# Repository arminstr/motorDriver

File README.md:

# Universal Motor Driver
This repository contains all files needed to order and build a motor driver which can be used with closed-loop stepper motors.

## Hardware
The driver is designed for board mount. THT pins are used for solder connection to a carrier board. Molex picoblade connectors are used for the encoder and CAN communication lines. These will be replaced by solder pins in a future revision.

## Software
Software features will be added continuously. Currently Microstepping and current control are implemented. Next added feature will be CAN communication. 

### Current State of Development

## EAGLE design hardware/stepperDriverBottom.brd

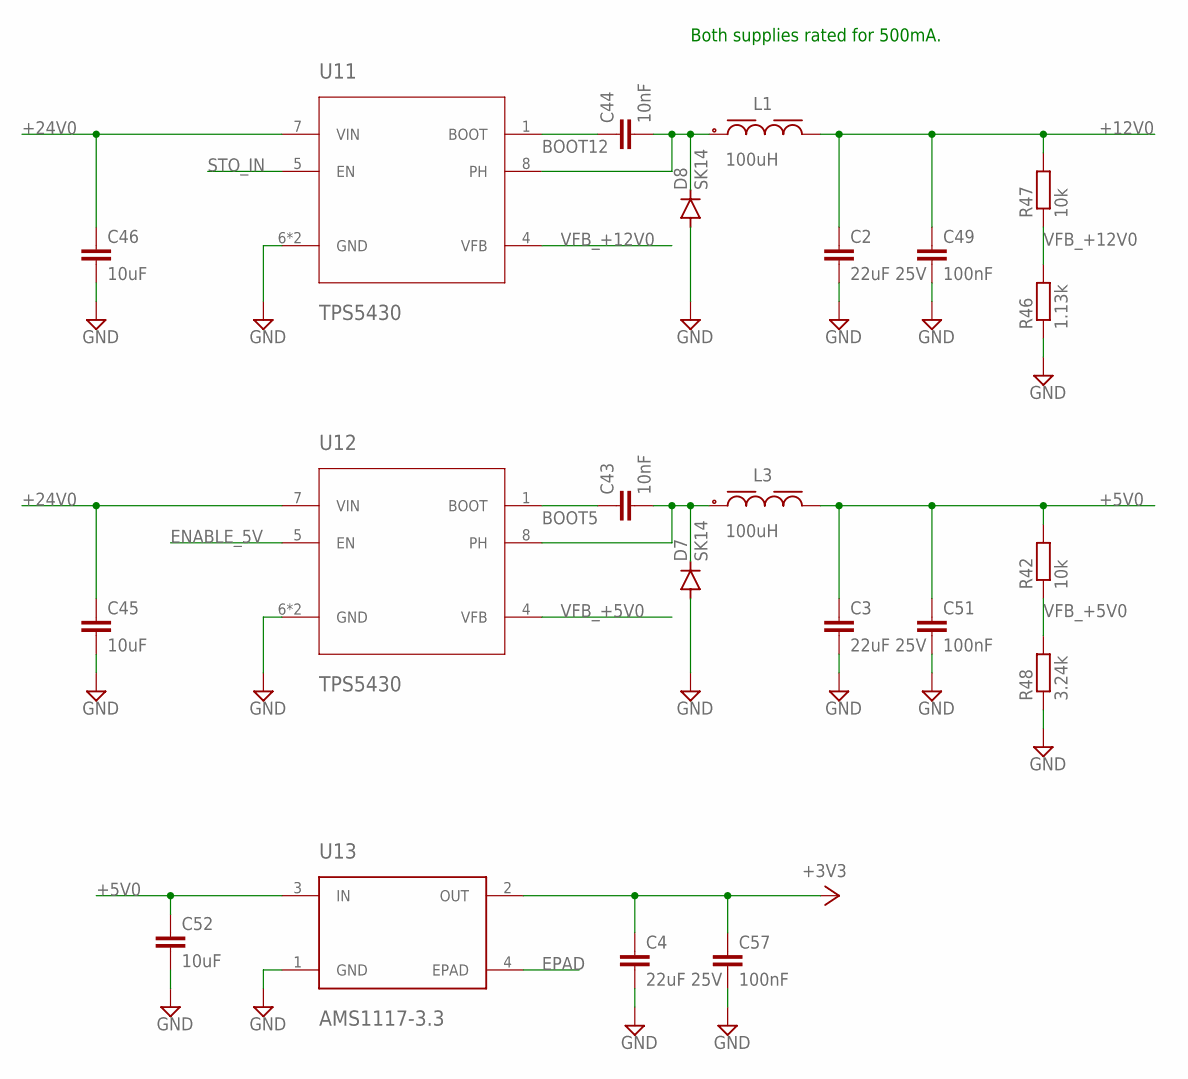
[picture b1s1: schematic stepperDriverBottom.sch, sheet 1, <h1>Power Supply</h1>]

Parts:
C2, C3, C4: 22uF 25V; C0805
C43, C44: 10nF; C0402
C45, C46, C52: 10uF; C1206
C49, C51, C57: 100nF; C0402
D7, D8: SK14; DO-214AC
L1, L3: 100uH; WE-LQS_6028
R42, R47: 10k; R0402
R46: 1.13k; R0402
R48: 3.24k; R0402
U11, U12: TPS5430; DDA8_3P1X2P4
U13: AMS1117-3.3; SOT223

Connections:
+3V3: C4.1, C57.1, U13.2 (OUT); also elsewhere on the board
+5V0: C3.1, C51.1, C52.1, L3.2, R42.2, U13.3 (IN); also elsewhere on the board
+12V0: C2.1, C49.1, L1.2, R47.2; also elsewhere on the board
+24V0: C45.1, C46.1, U11.7 (VIN), U12.7 (VIN); also elsewhere on the board
BOOT5: C43.1, U12.1 (BOOT)
BOOT12: C44.1, U11.1 (BOOT)
ENABLE_5V: U12.5 (EN)
EPAD: U13.4 (EPAD)
GND: C2.2, C3.2, C4.2, C45.2, C46.2, C49.2, C51.2, C52.2, C57.2, D7.A, D8.A, R46.1, R48.1, U11.6 (GND), U11.EPAD (GND), U12.6 (GND), U12.EPAD (GND), U13.1 (GND); also elsewhere on the board
unnamed: C44.2, D8.C, L1.1, U11.8 (PH)
unnamed: C43.2, D7.C, L3.1, U12.8 (PH)
STO_IN: U11.5 (EN); also elsewhere on the board
VFB_+5V0: R42.1, R48.2, U12.4 (VFB)
VFB_+12V0: R46.2, R47.1, U11.4 (VFB)

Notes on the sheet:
Both supplies rated for 500mA.

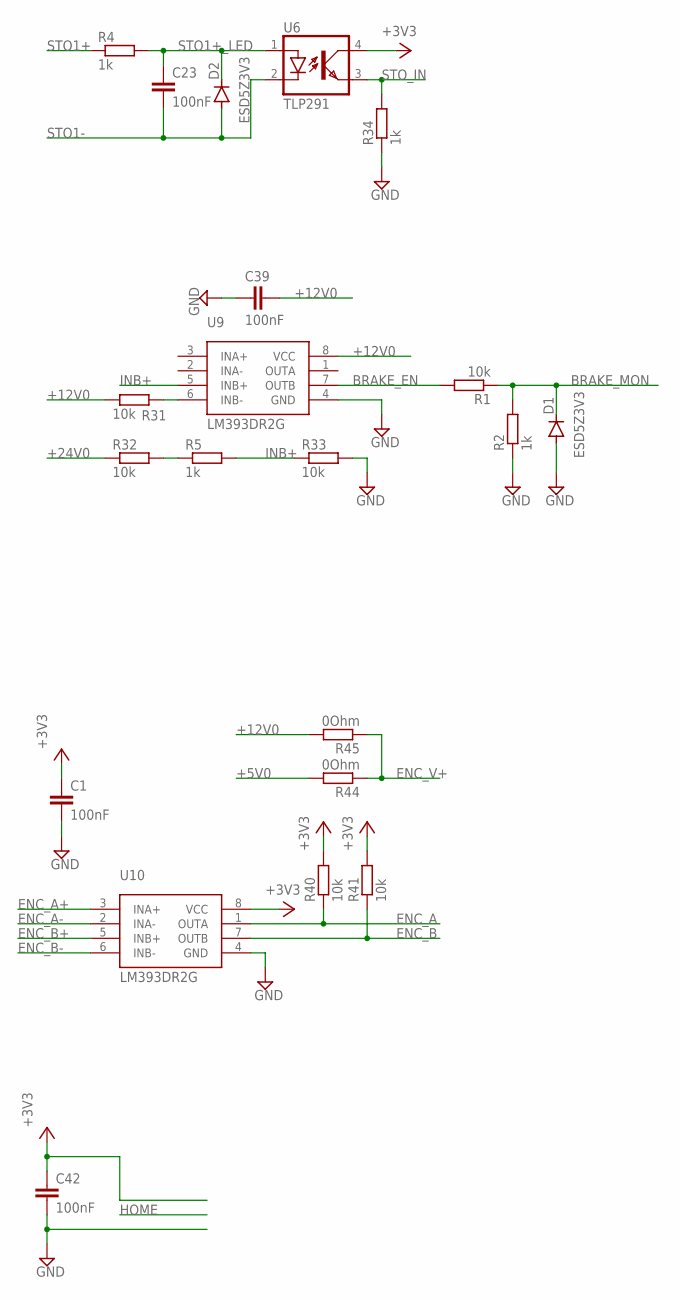
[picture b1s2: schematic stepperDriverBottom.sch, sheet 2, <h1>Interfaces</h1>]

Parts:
C1, C23, C39, C42: 100nF; C0402
D1, D2: ESD5Z3V3; SOD523
R1, R31, R32, R33, R40, R41: 10k; R0402
R2, R4, R5, R34: 1k; R0402
R44, R45: 0Ohm; R0402
U6: TLP291; SOIC127P700X210-4N
U9, U10: LM393DR2G; SOIC127P600X175-8N

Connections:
+3V3: C1.1, C42.1, R40.2, R41.2, U6.4 (COL), U10.8 (VCC); also elsewhere on the board
+5V0: R44.2; also elsewhere on the board
+12V0: C39.1, R31.1, R45.2, U9.8 (VCC); also elsewhere on the board
+24V0: R32.1; also elsewhere on the board
BRAKE_EN: R1.2, U9.7 (OUTB); also elsewhere on the board
BRAKE_MON: D1.C, R1.1, R2.2; also elsewhere on the board
ENC_A: R40.1, U10.1 (OUTA); also elsewhere on the board
ENC_A+: U10.3 (INA+); also elsewhere on the board
ENC_A-: U10.2 (INA-); also elsewhere on the board
ENC_B: R41.1, U10.7 (OUTB); also elsewhere on the board
ENC_B+: U10.5 (INB+); also elsewhere on the board
ENC_B-: U10.6 (INB-); also elsewhere on the board
ENC_V+: R44.1, R45.1; also elsewhere on the board
GND: C1.2, C39.2, C42.2, D1.A, R2.1, R33.2, R34.1, U9.4 (GND), U10.4 (GND); also elsewhere on the board
INB+: R5.2, R33.1, U9.5 (INB+)
unnamed: R5.1, R32.2
unnamed: R31.2, U9.6 (INB-)
STO1+: R4.1; also elsewhere on the board
STO1+_LED: C23.1, D2.C, R4.2, U6.1 (A)
STO1-: C23.2, D2.A, U6.2 (C); also elsewhere on the board
STO_IN: R34.2, U6.3 (EMIT); also elsewhere on the board

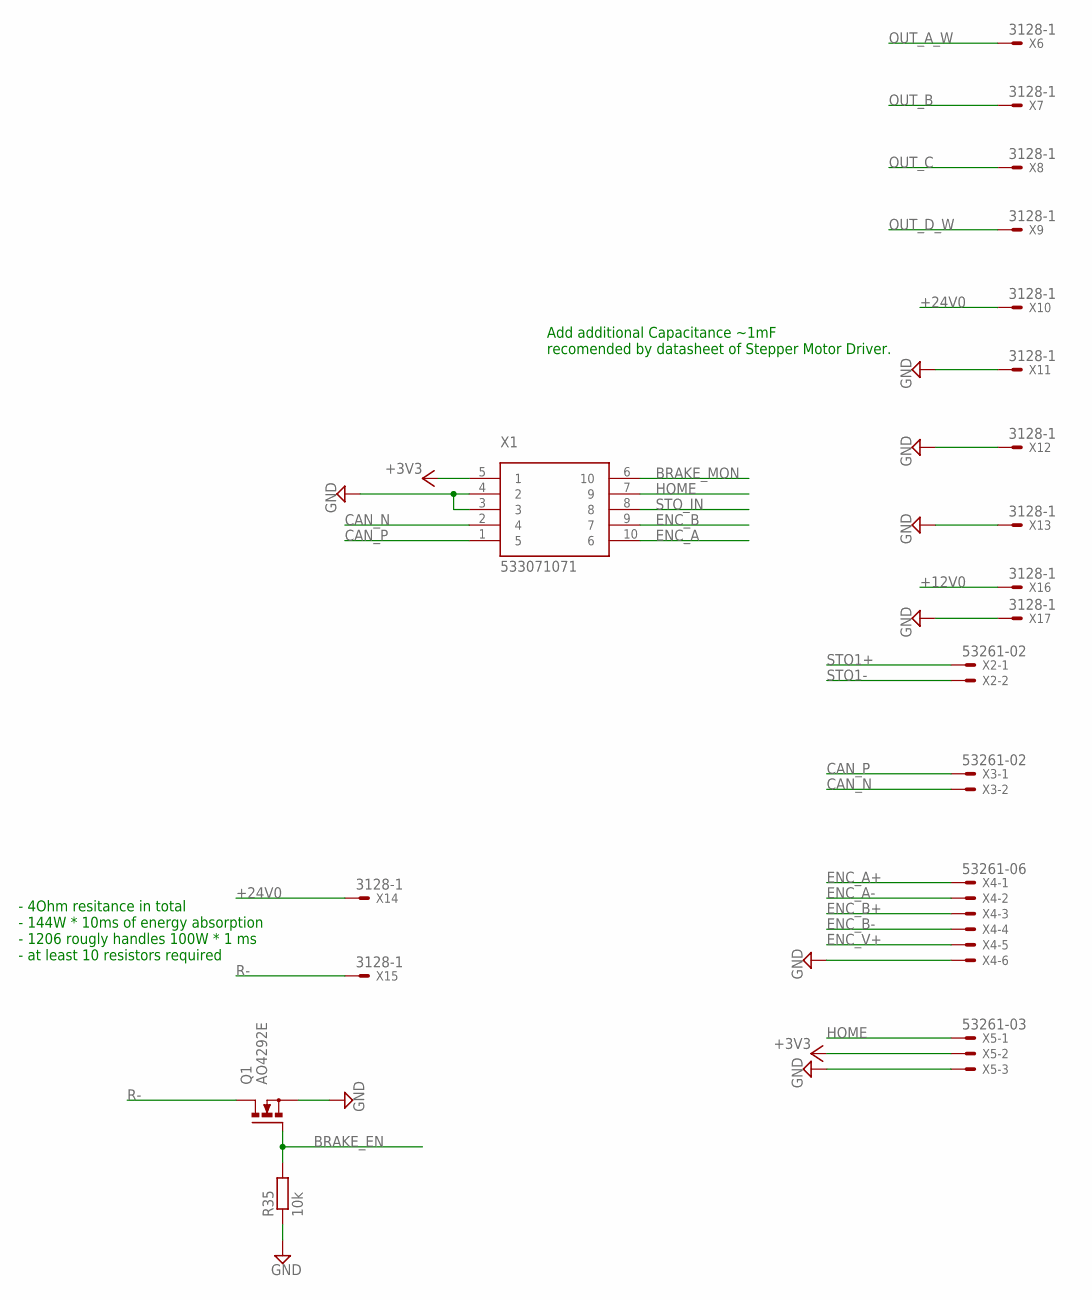
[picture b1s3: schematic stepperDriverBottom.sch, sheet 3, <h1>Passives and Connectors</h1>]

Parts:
Q1: AO4292E; SOIC127P600X175-8N
R35: 10k; R0402
X1: 533071071
X2, X3: 53261-02
X4: 53261-06
X5: 53261-03
X6, X7, X8, X9, X10, X11, X12, X13, X14, X15, X16, X17: 3128-1

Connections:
+3V3: X1.5 (1), X5.2; also elsewhere on the board
+12V0: X16.PIN1; also elsewhere on the board
+24V0: X10.PIN1, X14.PIN1; also elsewhere on the board
BRAKE_EN: Q1.4 (G), R35.2; also elsewhere on the board
BRAKE_MON: X1.6 (10); also elsewhere on the board
CAN_N: X1.2 (4), X3.2
CAN_P: X1.1 (5), X3.1
ENC_A: X1.10 (6); also elsewhere on the board
ENC_A+: X4.1; also elsewhere on the board
ENC_A-: X4.2; also elsewhere on the board
ENC_B: X1.9 (7); also elsewhere on the board
ENC_B+: X4.3; also elsewhere on the board
ENC_B-: X4.4; also elsewhere on the board
ENC_V+: X4.5; also elsewhere on the board
GND: Q1.1 (S), Q1.2 (S), Q1.3 (S), R35.1, X1.3, X1.4 (2), X4.6, X5.3, X11.PIN1, X12.PIN1, X13.PIN1, X17.PIN1; also elsewhere on the board
HOME: X1.7 (9), X5.1
OUT_A_W: X6.PIN1
OUT_B: X7.PIN1
OUT_C: X8.PIN1
OUT_D_W: X9.PIN1
R-: Q1.5 (D), Q1.6 (D), Q1.7 (D), Q1.8 (D), X15.PIN1
STO1+: X2.1; also elsewhere on the board
STO1-: X2.2; also elsewhere on the board
STO_IN: X1.8; also elsewhere on the board

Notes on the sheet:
- 4Ohm resitance in total - 144W * 10ms of energy absorption - 1206 rougly handles 100W * 1 ms - at least 10 resistors required
Add additional Capacitance ~1mF recomended by datasheet of Stepper Motor Driver.

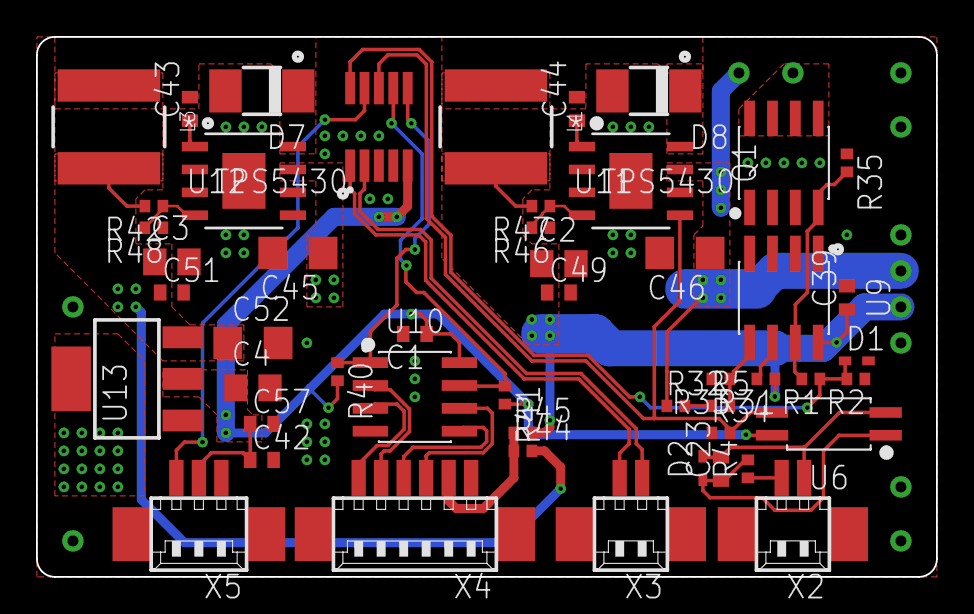
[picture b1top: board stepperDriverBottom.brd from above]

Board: 4 copper layers, 50.0 x 30.0 mm, 62 parts (0 on the bottom side), 31 nets.

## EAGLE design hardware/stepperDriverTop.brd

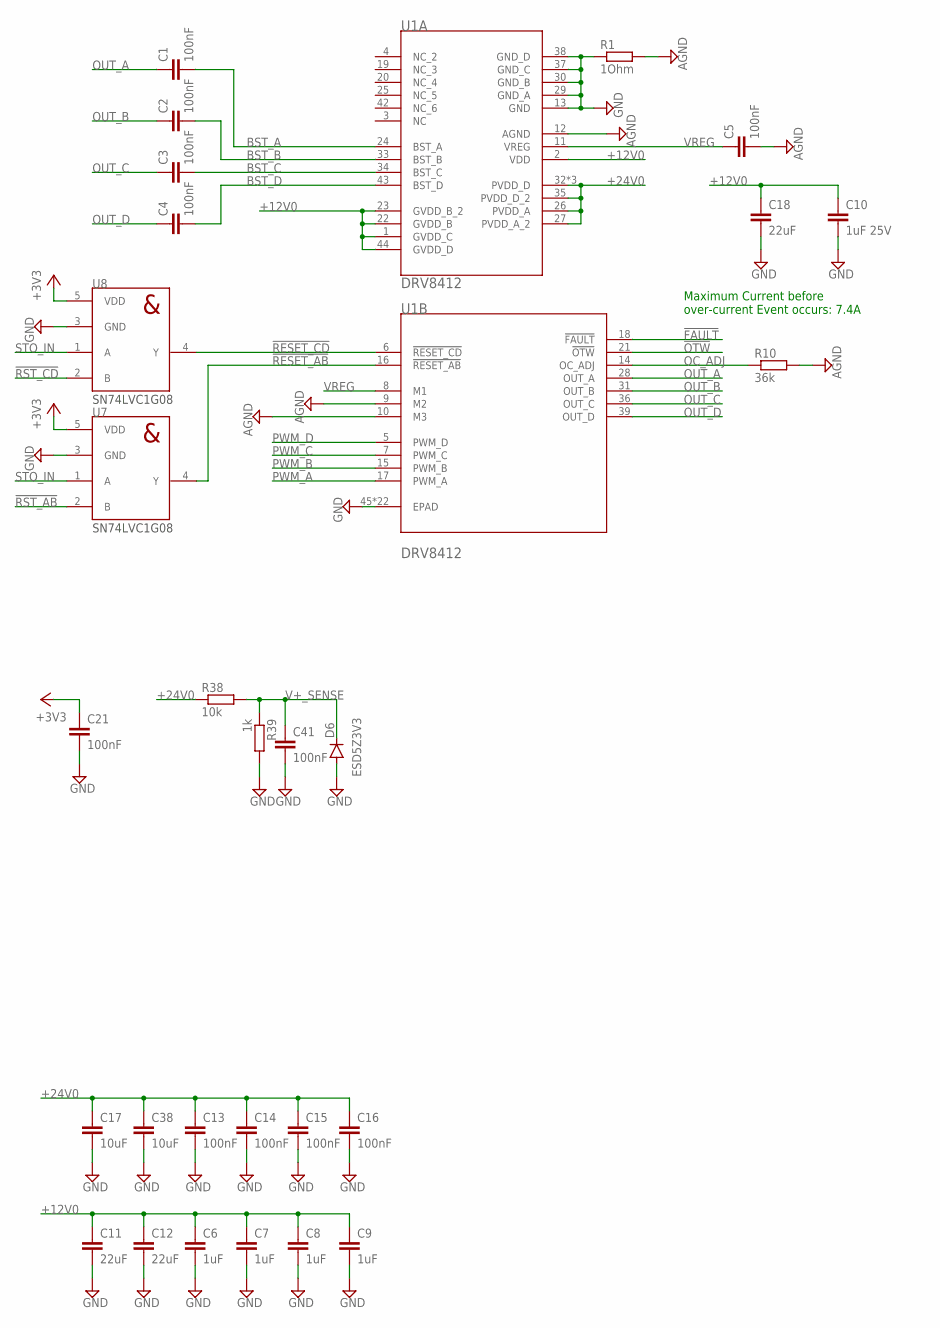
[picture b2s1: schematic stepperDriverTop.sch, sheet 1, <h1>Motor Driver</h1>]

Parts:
C1, C2, C3, C4: 100nF; C0603
C5, C13, C14, C15, C16, C21, C41: 100nF; C0402
C6, C7, C8, C9: 1uF; C0402
C10: 1uF 25V; C0402
C11, C12, C18: 22uF; C0805
C17, C38: 10uF; C1206
D6: ESD5Z3V3; SOD523
R1: 1Ohm; R0402
R10: 36k; R0402
R38: 10k; R0402
R39: 1k; R0402
U1: DRV8412; SOP63P810X120-45T350X740N
U7, U8: SN74LVC1G08; SOT95P240X110-5

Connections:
!FAULT: U1.18 (!FAULT); also elsewhere on the board
!OTW: U1.21 (!OTW); also elsewhere on the board
!RESET_AB: U1.16 (!RESET_AB), U7.4 (Y)
!RESET_CD: U1.6 (!RESET_CD), U8.4 (Y)
!RST_AB: U7.2 (B); also elsewhere on the board
!RST_CD: U8.2 (B); also elsewhere on the board
+3V3: C21.1, U7.5 (VDD), U8.5 (VDD); also elsewhere on the board
+12V0: C6.1, C7.1, C8.1, C9.1, C10.1, C11.1, C12.1, C18.1, U1.1 (GVDD_C), U1.2 (VDD), U1.22 (GVDD_B), U1.23 (GVDD_B_2), U1.44 (GVDD_D); also elsewhere on the board
+24V0: C13.1, C14.1, C15.1, C16.1, C17.1, C38.1, R38.1, U1.26 (PVDD_A), U1.27 (PVDD_A_2), U1.32 (PVDD_D), U1.35 (PVDD_D_2), U1.40 (PVDD_D), U1.41 (PVDD_D); also elsewhere on the board
AGND: C5.2, R1.2, R10.2, U1.9 (M2), U1.10 (M3), U1.12 (AGND)
BST_A: C1.2, U1.24 (BST_A)
BST_B: C2.2, U1.33 (BST_B)
BST_C: C3.2, U1.34 (BST_C)
BST_D: C4.2, U1.43 (BST_D)
GND: C6.2, C7.2, C8.2, C9.2, C10.2, C11.2, C12.2, C13.2, C14.2, C15.2, C16.2, C17.2, C18.2, C21.2, C38.2, C41.2, D6.A, R1.1, R39.2, U1.13 (GND), U1.29 (GND_A), U1.30 (GND_B), U1.37 (GND_C), U1.38 (GND_D), U1.45 (EPAD), U1.V_1 (EPAD), U1.V_2 (EPAD), U1.V_3 (EPAD), U1.V_4 (EPAD), U1.V_5 (EPAD), U1.V_6 (EPAD), U1.V_7 (EPAD), U1.V_8 (EPAD), U1.V_9 (EPAD), U1.V_10 (EPAD), U1.V_11 (EPAD), U1.V_12 (EPAD), U1.V_13 (EPAD), U1.V_14 (EPAD), U1.V_15 (EPAD), U1.V_16 (EPAD), U1.V_17 (EPAD), U1.V_18 (EPAD), U1.V_19 (EPAD), U1.V_20 (EPAD), U1.V_21 (EPAD), U7.3 (GND), U8.3 (GND); also elsewhere on the board
OC_ADJ: R10.1, U1.14 (OC_ADJ)
OUT_A: C1.1, U1.28 (OUT_A); also elsewhere on the board
OUT_B: C2.1, U1.31 (OUT_B); also elsewhere on the board
OUT_C: C3.1, U1.36 (OUT_C); also elsewhere on the board
OUT_D: C4.1, U1.39 (OUT_D); also elsewhere on the board
PWM_A: U1.17 (PWM_A); also elsewhere on the board
PWM_B: U1.15 (PWM_B); also elsewhere on the board
PWM_C: U1.7 (PWM_C); also elsewhere on the board
PWM_D: U1.5 (PWM_D); also elsewhere on the board
STO_IN: U7.1 (A), U8.1 (A); also elsewhere on the board
V+_SENSE: C41.1, D6.C, R38.2, R39.1; also elsewhere on the board
VREG: C5.1, U1.8 (M1), U1.11 (VREG)

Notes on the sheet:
Maximum Current before over-current Event occurs: 7.4A

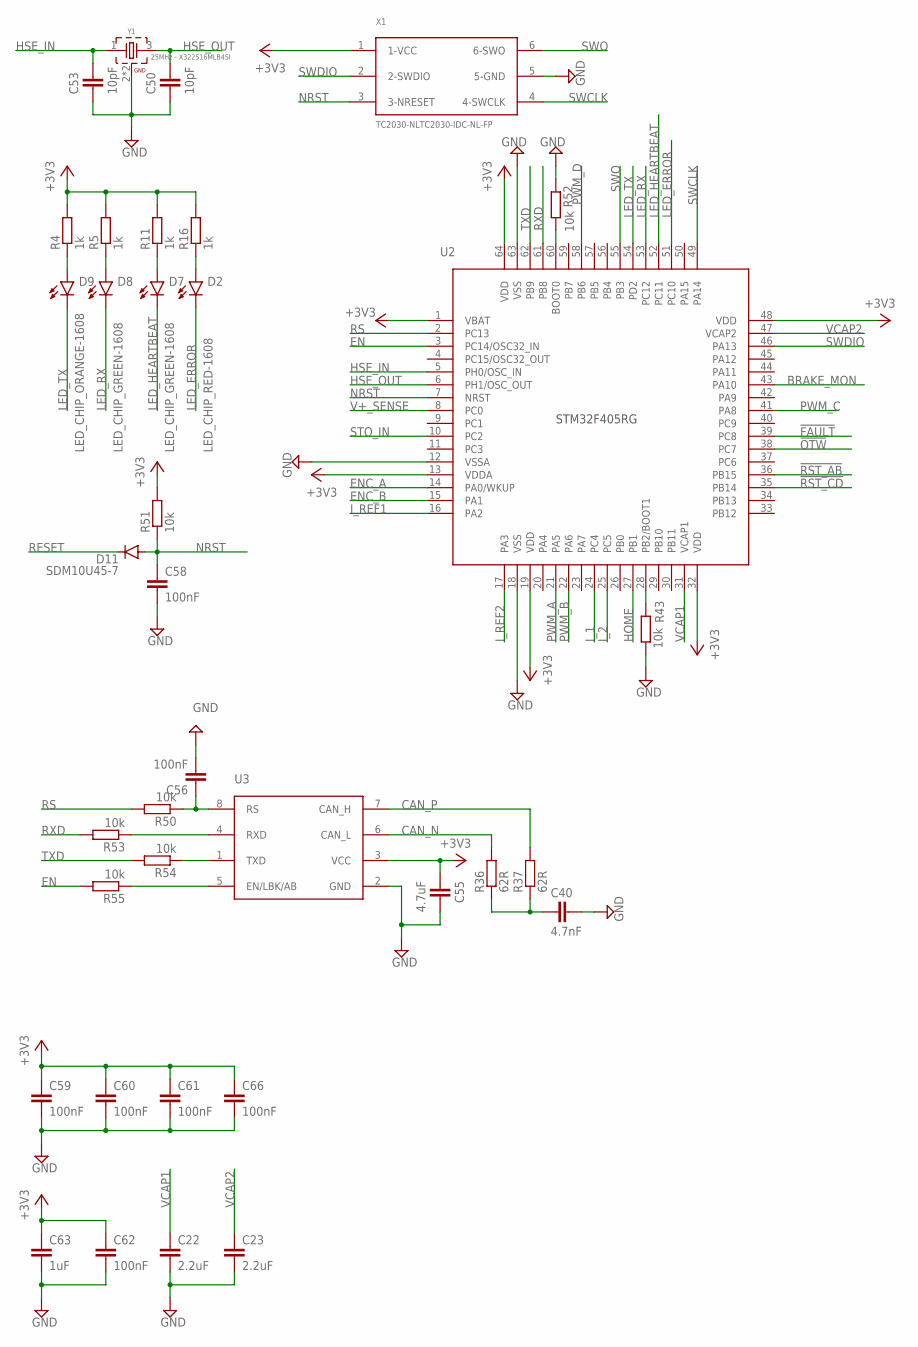
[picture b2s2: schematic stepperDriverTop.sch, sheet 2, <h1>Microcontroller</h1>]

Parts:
C22, C23: 2.2uF; C0603
C40: 4.7nF; C0402
C50, C53: 10pF; C0402
C55: 4.7uF; C0402
C56, C58, C59, C60, C61, C62, C66: 100nF; C0402
C63: 1uF; C0402
D2: LED_CHIP_RED-1608; LEDC1608X39N_R
D7, D8: LED_CHIP_GREEN-1608; LEDC1608X39N_G
D9: LED_CHIP_ORANGE-1608; LEDC1608X39N_G
D11: SDM10U45-7; SOD523
R4, R5, R11, R16: 1k; R0402
R36, R37: 62R; R0603
R43, R50, R51, R52, R53, R54, R55: 10k; R0402
U2: STM32F405RGLQFP64; QFP50P1200X1200X120-64
U3: SN65HVD23X-Q1D0008A; SOIC127P599X175-8N
X1: TC2030-NLTC2030-IDC-NL-FP; TC2030-NL
Y1: 25MHz - X322516MLB4SI; WE-XTAL_CFPX-180

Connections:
!FAULT: U2.39 (PC8); also elsewhere on the board
!OTW: U2.38 (PC7); also elsewhere on the board
!RST_AB: U2.36 (PB15); also elsewhere on the board
!RST_CD: U2.35 (PB14); also elsewhere on the board
+3V3: C55.2, C59.1, C60.1, C61.1, C62.1, C63.1, C66.1, R4.2, R5.2, R11.2, R16.2, R51.2, U2.1 (VBAT), U2.13 (VDDA), U2.19 (VDD), U2.32 (VDD), U2.48 (VDD), U2.64 (VDD), U3.3 (VCC), X1.1 (1-VCC); also elsewhere on the board
BRAKE_MON: U2.43 (PA10); also elsewhere on the board
CAN_N: R36.2, U3.6 (CAN_L); also elsewhere on the board
CAN_P: R37.2, U3.7 (CAN_H); also elsewhere on the board
EN: R55.2, U2.3 (PC14/OSC32_IN)
ENC_A: U2.14 (PA0/WKUP); also elsewhere on the board
ENC_B: U2.15 (PA1); also elsewhere on the board
GND: C22.2, C23.2, C40.1, C50.2, C53.2, C55.1, C56.2, C58.2, C59.2, C60.2, C61.2, C62.2, C63.2, C66.2, R43.1, R52.1, U2.12 (VSSA), U2.18 (VSS), U2.63 (VSS), U3.2 (GND), X1.5 (5-GND), Y1.2 (GND), Y1.4 (GND); also elsewhere on the board
HOME: U2.27 (PB1); also elsewhere on the board
HSE_IN: C53.1, U2.5 (PH0/OSC_IN), Y1.1
HSE_OUT: C50.1, U2.6 (PH1/OSC_OUT), Y1.3 (2)
I_1: U2.24 (PC4); also elsewhere on the board
I_2: U2.25 (PC5); also elsewhere on the board
I_REF1: U2.16 (PA2); also elsewhere on the board
I_REF2: U2.17 (PA3); also elsewhere on the board
LED_ERROR: D2.1 (C), U2.51 (PC10)
LED_HEARTBEAT: D7.1 (C), U2.52 (PC11)
LED_RX: D8.1 (C), U2.53 (PC12)
LED_TX: D9.1 (C), U2.54 (PD2)
unnamed: D9.2 (A), R4.1
unnamed: D8.2 (A), R5.1
unnamed: D7.2 (A), R11.1
unnamed: D2.2 (A), R16.1
unnamed: C40.2, R36.1, R37.1
unnamed: R43.2, U2.28 (PB2/BOOT1)
unnamed: R52.2, U2.60 (BOOT0)
unnamed: C56.1, R50.1, U3.8 (RS)
unnamed: R53.1, U3.4 (RXD)
unnamed: R54.1, U3.1 (TXD)
unnamed: R55.1, U3.5 (EN/LBK/AB)
NRST: C58.1, D11.A, R51.1, U2.7 (NRST), X1.3 (3-NRESET)
PWM_A: U2.21 (PA5); also elsewhere on the board
PWM_B: U2.22 (PA6); also elsewhere on the board
PWM_C: U2.41 (PA8); also elsewhere on the board
PWM_D: U2.58 (PB6); also elsewhere on the board
RESET: D11.C
RS: R50.2, U2.2 (PC13)
RXD: R53.2, U2.61 (PB8)
STO_IN: U2.10 (PC2); also elsewhere on the board
SWCLK: U2.49 (PA14), X1.4 (4-SWCLK)
SWDIO: U2.46 (PA13), X1.2 (2-SWDIO)
SWO: U2.55 (PB3), X1.6 (6-SWO)
TXD: R54.2, U2.62 (PB9)
V+_SENSE: U2.8 (PC0); also elsewhere on the board
VCAP1: C22.1, U2.31 (VCAP1)
VCAP2: C23.1, U2.47 (VCAP2)

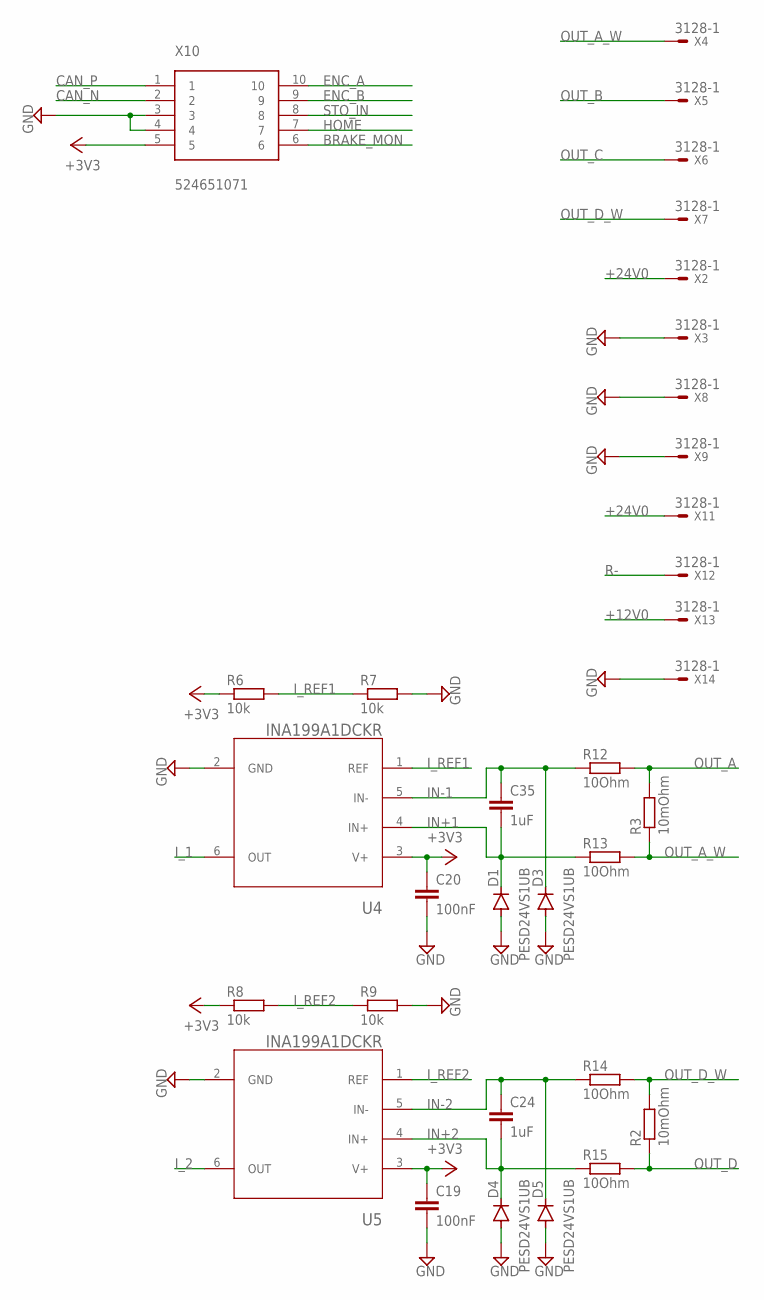
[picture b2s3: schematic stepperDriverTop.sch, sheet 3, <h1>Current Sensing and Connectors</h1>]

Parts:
C19, C20: 100nF; C0402
C24, C35: 1uF; C0402
D1, D3, D4, D5: PESD24VS1UB; SOD523
R2, R3: 10mOhm; R0805
R6, R7, R8, R9: 10k; R0402
R12, R13, R14, R15: 10Ohm; R0402
U4, U5: INA199A1DCKR; SOP65P210X110-6N
X2, X3, X4, X5, X6, X7, X8, X9, X11, X12, X13, X14: 3128-1
X10: 524651071

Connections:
+3V3: C19.1, C20.1, R6.1, R8.1, U4.3 (V+), U5.3 (V+), X10.5; also elsewhere on the board
+12V0: X13.PIN1; also elsewhere on the board
+24V0: X2.PIN1, X11.PIN1; also elsewhere on the board
BRAKE_MON: X10.6; also elsewhere on the board
CAN_N: X10.2; also elsewhere on the board
CAN_P: X10.1; also elsewhere on the board
ENC_A: X10.10; also elsewhere on the board
ENC_B: X10.9; also elsewhere on the board
GND: C19.2, C20.2, D1.A, D3.A, D4.A, D5.A, R7.2, R9.2, U4.2 (GND), U5.2 (GND), X3.PIN1, X8.PIN1, X9.PIN1, X10.3, X10.4, X14.PIN1; also elsewhere on the board
HOME: X10.7; also elsewhere on the board
IN+1: C35.2, D1.C, R13.1, U4.4 (IN+)
IN+2: C24.2, D4.C, R15.1, U5.4 (IN+)
IN-1: C35.1, D3.C, R12.1, U4.5 (IN-)
IN-2: C24.1, D5.C, R14.1, U5.5 (IN-)
I_1: U4.6 (OUT); also elsewhere on the board
I_2: U5.6 (OUT); also elsewhere on the board
I_REF1: R6.2, R7.1, U4.1 (REF); also elsewhere on the board
I_REF2: R8.2, R9.1, U5.1 (REF); also elsewhere on the board
OUT_A: R3.2, R12.2; also elsewhere on the board
OUT_A_W: R3.1, R13.2, X4.PIN1
OUT_B: X5.PIN1; also elsewhere on the board
OUT_C: X6.PIN1; also elsewhere on the board
OUT_D: R2.1, R15.2; also elsewhere on the board
OUT_D_W: R2.2, R14.2, X7.PIN1
R-: X12.PIN1
STO_IN: X10.8; also elsewhere on the board

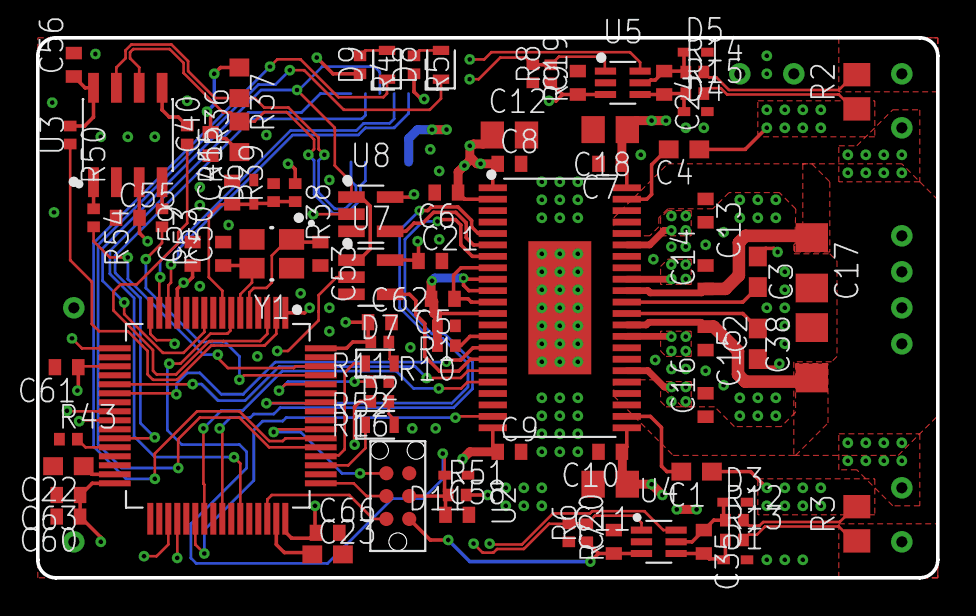
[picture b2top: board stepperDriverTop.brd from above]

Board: 4 copper layers, 50.0 x 30.0 mm, 98 parts (1 on the bottom side), 70 nets.

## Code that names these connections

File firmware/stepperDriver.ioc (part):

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Mcu.Name=STM32F405RGTx
Mcu.Package=LQFP64
Mcu.UserName=STM32F405RGTx
PA0-WKUP.GPIOParameters=GPIO_PuPd,GPIO_Label
PA0-WKUP.GPIO_Label=ENC_A
PA0-WKUP.GPIO_PuPd=GPIO_PULLUP
PA0-WKUP.Signal=S_TIM5_CH1
PA1.GPIOParameters=GPIO_PuPd,GPIO_Label
PA1.GPIO_Label=ENC_B
PA1.GPIO_PuPd=GPIO_PULLUP
PA1.Signal=S_TIM5_CH2
PA10.GPIOParameters=GPIO_Label,GPIO_ModeDefaultEXTI
PA10.GPIO_Label=BRAKE_MON
PA10.GPIO_ModeDefaultEXTI=GPIO_MODE_IT_RISING_FALLING
PA10.Signal=GPXTI10
PA13.Mode=Trace_Asynchronous_SW
PA13.Signal=SYS_JTMS-SWDIO
PA14.Mode=Trace_Asynchronous_SW
PA14.Signal=SYS_JTCK-SWCLK
PA2.GPIOParameters=GPIO_Label
PA2.GPIO_Label=IREF_1
PA2.Signal=ADCx_IN2
PA3.GPIOParameters=GPIO_Label
PA3.GPIO_Label=IREF_2
PA3.Signal=ADCx_IN3
PA5.GPIOParameters=GPIO_Label
PA5.GPIO_Label=PWM_A
PA5.Signal=S_TIM2_CH1_ETR
PA6.GPIOParameters=GPIO_Label
PA6.GPIO_Label=PWM_B
PA6.Signal=S_TIM3_CH1
PA8.GPIOParameters=GPIO_Label
PA8.GPIO_Label=PWM_C
PA8.Signal=S_TIM1_CH1
PB1.GPIOParameters=GPIO_Label
PB1.GPIO_Label=HOME_IN
PB1.Signal=ADCx_IN9
PB14.GPIOParameters=GPIO_Label
PB14.GPIO_Label=NRST_CD
PB14.Signal=GPIO_Output
PB15.GPIOParameters=GPIO_Label
PB15.GPIO_Label=NRST_AB
PB15.Signal=GPIO_Output
PB2.GPIOParameters=GPIO_Label
PB2.GPIO_Label=BOOT1
PB2.Signal=GPIO_Input
PB3.Mode=Trace_Asynchronous_SW
PB3.Signal=SYS_JTDO-SWO
PB6.GPIOParameters=GPIO_Label
PB6.GPIO_Label=PWM_D
PB6.Signal=S_TIM4_CH1
PB8.Mode=Master
PB8.Signal=CAN1_RX
PB9.Mode=Master
PB9.Signal=CAN1_TX
PC0.GPIOParameters=GPIO_Label
PC0.GPIO_Label=V+_SENSE
PC0.Signal=ADCx_IN10
PC10.GPIOParameters=PinState,GPIO_Label
PC10.GPIO_Label=LED_ERROR
PC10.PinState=GPIO_PIN_SET
PC10.Signal=GPIO_Output
PC11.GPIOParameters=PinState,GPIO_Label
PC11.GPIO_Label=LED_HEARTBEAT
PC11.PinState=GPIO_PIN_SET
PC11.Signal=GPIO_Output
PC12.GPIOParameters=PinState,GPIO_Label
PC12.GPIO_Label=LED_RX
PC12.PinState=GPIO_PIN_SET
PC12.Signal=GPIO_Output
PC13-ANTI_TAMP.GPIOParameters=GPIO_Label
PC13-ANTI_TAMP.GPIO_Label=CAN1_RS
PC13-ANTI_TAMP.Signal=GPIO_Input
PC14-OSC32_IN.GPIOParameters=GPIO_Label
PC14-OSC32_IN.GPIO_Label=CAN1_EN
PC14-OSC32_IN.Signal=GPIO_Output
PC2.GPIOParameters=GPIO_Label,GPIO_ModeDefaultEXTI
PC2.GPIO_Label=STO_IN
PC2.GPIO_ModeDefaultEXTI=GPIO_MODE_IT_RISING_FALLING
PC2.Signal=GPXTI2
PC4.GPIOParameters=GPIO_Label
PC4.GPIO_Label=I_1
PC4.Signal=ADCx_IN14
PC5.GPIOParameters=GPIO_Label
PC5.GPIO_Label=I_2
PC5.Signal=ADCx_IN15
PC7.GPIOParameters=GPIO_Label,GPIO_ModeDefaultEXTI
PC7.GPIO_Label=NOTW
PC7.GPIO_ModeDefaultEXTI=GPIO_MODE_IT_RISING_FALLING
PC7.Signal=GPXTI7
PC8.GPIOParameters=GPIO_Label,GPIO_ModeDefaultEXTI
PC8.GPIO_Label=NFAULT
PC8.GPIO_ModeDefaultEXTI=GPIO_MODE_IT_RISING_FALLING
PC8.Signal=GPXTI8
PD2.GPIOParameters=PinState,GPIO_Label
PD2.GPIO_Label=LED_TX
PD2.PinState=GPIO_PIN_SET
PD2.Signal=GPIO_Output
PH0-OSC_IN.Mode=HSE-External-Oscillator
PH0-OSC_IN.Signal=RCC_OSC_IN
PH1-OSC_OUT.Mode=HSE-External-Oscillator
PH1-OSC_OUT.Signal=RCC_OSC_OUT
RCC.HSE_VALUE=25000000
RCC.SYSCLKFreq_VALUE=168000000
RCC.SYSCLKSource=RCC_SYSCLKSOURCE_PLLCLK
board=custom

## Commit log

2021-01-15 removed Eagle Backup Files
2021-01-15 renamed folder
2021-01-15 added Firmware
2021-01-15 Create LICENSE
2021-01-15 added README
2021-01-15 addd gif

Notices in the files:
parts and their libraries:
Wurth_Power Magnetics_WE-LQS: Copyright: Würth Elektronik
